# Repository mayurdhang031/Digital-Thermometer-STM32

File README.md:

# Digital Thermometer using STM32

## Overview
A digital thermometer PCB designed using KiCad and based on the STM32 microcontroller. The system measures temperature using an LM35 sensor and can be integrated with a display for real-time temperature monitoring.

## Features
- STM32 Microcontroller
- LM35 Temperature Sensor
- KiCad PCB Design
- 2-Layer PCB
- Embedded C Firmware

## Software Used
- KiCad
- STM32CubeIDE
- Embedded C

## Hardware
- STM32 Microcontroller
- LM35 Temperature sensor
- 16*2 LCD
- Resistors
- Capacitors
- Crystal Oscillator

## Repository Contents
- Schematic (.kicad_sch)
- PCB Layout (.kicad_pcb)
- KiCad Project (.kicad_pro)

## Author
Mayur Dhang

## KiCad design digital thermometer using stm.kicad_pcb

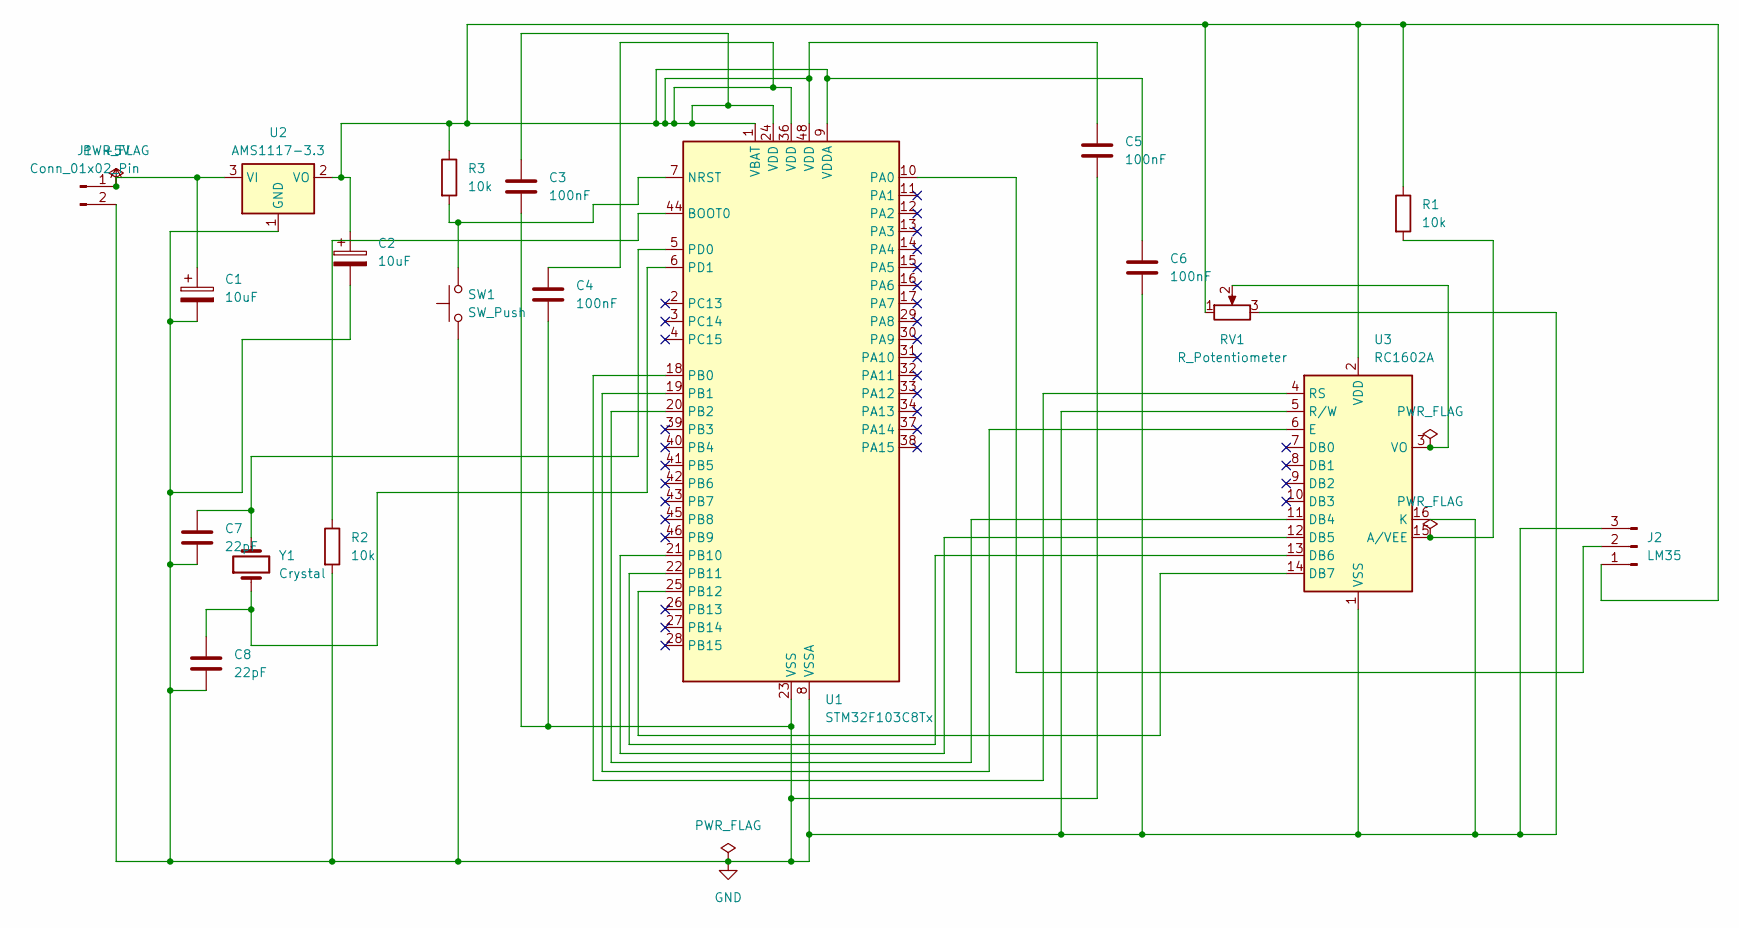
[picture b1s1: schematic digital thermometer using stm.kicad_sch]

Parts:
C1, C2: 10uF; CP_Radial_D5.0mm_P2.00mm
C3, C4, C5, C6: 100nF; C_Disc_D5.0mm_W2.5mm_P5.00mm
C7, C8: 22pF; C_Disc_D5.0mm_W2.5mm_P5.00mm
J1: Conn_01x02_Pin; PinHeader_1x02_P2.54mm_Vertical
J2: LM35; PinHeader_1x03_P2.54mm_Vertical
R1, R2, R3: 10k; R_Axial_DIN0207_L6.3mm_D2.5mm_P7.62mm_Horizontal
RV1: R_Potentiometer; Potentiometer_Bourns_3296W_Vertical
SW1: SW_Push; SW_PUSH_6mm
U1: STM32F103C8Tx; LQFP-48_7x7mm_P0.5mm
U2: AMS1117-3.3; SOT-223-3_TabPin2
U3: RC1602A
Y1: Crystal; Crystal_HC49-U_Vertical

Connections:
+5V: C1.1, J1.1, U2.3 (VI)
GND: C1.2, C2.2, C3.2, C4.2, C5.2, C6.2, C7.2, C8.2, J1.2, J2.3, R2.2, RV1.3, SW1.1, U1.8 (VSSA), U1.23 (VSS), U1.35 (VSS), U1.47 (VSS), U2.1 (GND), U3.1 (VSS), U3.5 (R/W), U3.16 (K)
unnamed: C2.1, C3.1, C4.1, C5.1, C6.1, J2.1, R1.1, R3.1, RV1.1, U1.1 (VBAT), U1.9 (VDDA), U1.24 (VDD), U1.36 (VDD), U1.48 (VDD), U2.2 (VO), U3.2 (VDD)
unnamed: J2.2, U1.10 (PA0)
unnamed: R2.1, U1.44 (BOOT0)
unnamed: R3.2, SW1.2, U1.7 (NRST)
unnamed: U1.18 (PB0), U3.4 (RS)
unnamed: U1.19 (PB1), U3.6 (E)
unnamed: U1.20 (PB2), U3.11 (DB4)
unnamed: U1.21 (PB10), U3.12 (DB5)
unnamed: U1.22 (PB11), U3.13 (DB6)
unnamed: U1.25 (PB12), U3.14 (DB7)
unnamed: C7.1, U1.5 (PD0), Y1.2
unnamed: C8.1, U1.6 (PD1), Y1.1
unnamed: R1.2, U3.15 (A/VEE)
unnamed: RV1.2, U3.3 (VO)

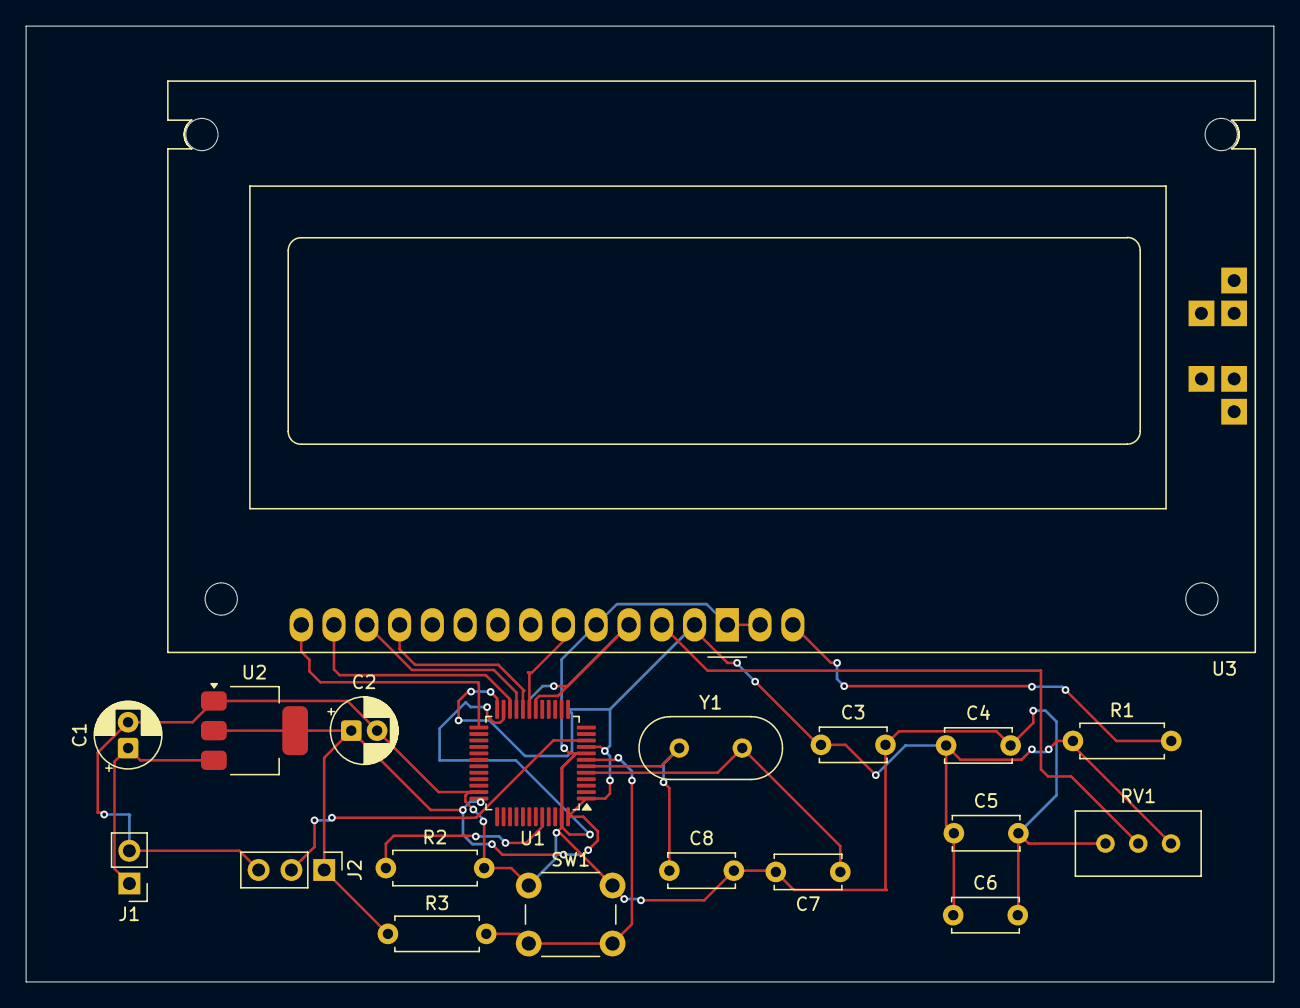
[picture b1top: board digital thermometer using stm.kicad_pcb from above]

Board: 2 copper layers, 96.7 x 74.1 mm, 19 parts (0 on the bottom side), 16 nets.
